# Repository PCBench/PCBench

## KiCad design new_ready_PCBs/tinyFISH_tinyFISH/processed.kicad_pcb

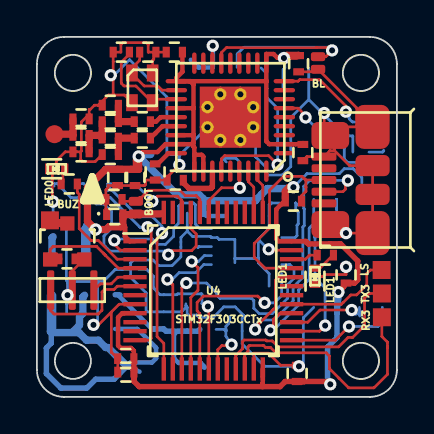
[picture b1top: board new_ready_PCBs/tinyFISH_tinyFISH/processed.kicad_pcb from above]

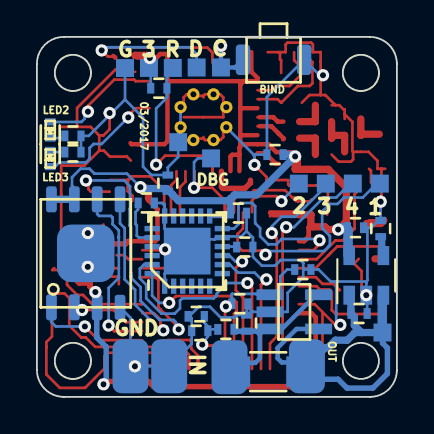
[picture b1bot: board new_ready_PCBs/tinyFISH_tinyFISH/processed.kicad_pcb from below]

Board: 2 copper layers, 20.0 x 20.0 mm, 87 parts (40 on the bottom side), 56 nets.

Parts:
ANT1: TP; smd_1x1_round
BIND1: CUSTOM_PUSHBUTTON; OMRON_B3U-3000P
BL1: BL; SOLDERBRIDGE
C1, C10, C17, C23: 1u; C_0402_CUSTOM
C2, C6: 12p; C_0402_CUSTOM
C3, C13, C14, C16, C19, C20, C21, C22, C25, C26, C27, C29: 100n; C_0402_CUSTOM
C4, C7: 100p; C_0402_CUSTOM
C5: 220p; C_0402_CUSTOM
C8, C9: 1p; C_0402_CUSTOM
C11: 1p8; C_0402_CUSTOM
C12: 1p5; C_0402_CUSTOM
C15: 2n2; C_0402_CUSTOM
C18: 4u7; C_0402_CUSTOM
C24, C30: 10n; C_0402_CUSTOM
C28: NC; C_0402_CUSTOM
DEBUG1: TP; TP_1x1
GND_IN1: GND; PAD_2x3
GND_MOUNT_2: GND; TP_1x1
GND_OUT1: GND; PAD_2x3
H1, H2, H3, H4: hole; mouting_hole
ISP_3V1: TP; TP_1x1
ISP_CLOCK1: TP; TP_1x1
ISP_DATA1: TP; TP_1x1
ISP_GND1: TP; TP_1x1
JP0: BOOT0; SOLDERBRIDGE
L1, L2, L3: 1.2nH; L_0402_CUSTOM
LED0: BLUE; LED_0402
LED1, LED3: RED; LED_0402
LED2: GREEN; LED_0402
Q1: SI2302DS; SI2302DS_SOT-23
R1, R5, R10: 10k; R_0402_CUSTOM
R3: 56k; R_0402_CUSTOM
R4: 220; R_0402_CUSTOM
R6, R8: 330; R_0402_CUSTOM
R7: 100; R_0402_CUSTOM
R9: 1k5; R_0402_CUSTOM
R11, R501: 1k; R_0402_CUSTOM
R12: 0R005; R_1206
R13: 30k; R_0402_CUSTOM
TP_1: WS2812; TP_1x1
TP_2: UART3_RX; TP_1x1
TP_3: UART3_RX1; TP_1x1
TP_4: BUZZER_GND; TP_1x1
TP_5: BUZZER_VCC; TP_1x1
TP_ESC_0: ESC_0; TP_1x1
TP_ESC_1: ESC_1; TP_1x1
TP_ESC_2: ESC_2; TP_1x1
TP_ESC_3: ESC_3; TP_1x1
U1: CC2510; QFN36_CC2510
U2: MPU-6000; QFN-24
U3: LP2985AIM5-3.0/NOPB; SOT-23-5
U4: STM32F303CCTx; LQFP-48_7x7mm_Pitch0.5mm
U5: M25P16-VME; VFDFPN8
U6: MICRO_USB_B; USB_MICRO_MOLEX
U7: INA139; DBV
VBAT1: CONN_1; PAD_2x3
VBAT_IN1: CONN_1; PAD_2x3
X1: 26MHz; crystal_2016
X2: 8MHz; CSTCE_G_A

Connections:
3V: C3.1, C5.1, C10.1, C13.1, C16.2, C18.1, C19.1, C20.1, C21.1, C22.1, C23.1, C24.1, C25.1, C29.1, ISP_3V1.1, JP0.1, R5.1, R9.1, U1.2, U1.10, U1.19, U1.22, U1.25, U1.26, U1.28, U1.29, U2.13, U3.5, U4.1, U4.9, U4.24, U4.36, U4.48, U5.3, U5.7, U5.8
/power/BAT+: C26.2, R10.2, R12.1, U7.3, U7.5, VBAT_IN1.1
/rx/ANT_N: C4.1, U1.24
/rx/ANT_P: C7.1, U1.23
/rx/ISP_CLOCK: BIND1.1, ISP_CLOCK1.1, U1.16
/rx/ISP_DATA: BL1.1, ISP_DATA1.1, U1.15
/rx/~RESET: R5.2, U1.31
ADC_CURRENT: C28.2, R13.1, U4.18, U7.1
ADC_VBAT: C27.1, R10.1, R11.2, U4.19
BUZZER: Q1.D, TP_4.1
BUZZER_IO: Q1.G, R501.2, U4.4
ESC_0: TP_ESC_0.1, U4.45
ESC_1: TP_ESC_1.1, U4.46
ESC_2: TP_ESC_2.1, U4.13
ESC_3: TP_ESC_3.1, U4.12
FLASH_CS: U4.25, U5.1
FLASH_MISO: U4.27, U5.2
FLASH_MOSI: U4.28, U5.5
FLASH_SCK: U4.26, U5.6
GND: BIND1.2, BL1.2, C1.1, C2.2, C3.2, C5.2, C6.2, C8.1, C10.2, C11.1, C12.1, C13.2, C14.2, C15.1, C16.1, C17.2, C18.2, C19.2, C20.2, C21.2, C22.2, C23.2, C24.2, C25.2, C26.1, C27.2, C28.1, C29.2, C30.2, GND_IN1.1, GND_MOUNT_2.1, GND_OUT1.1, ISP_GND1.1, L1.1, LED0.1, LED1.1, Q1.S, R1.2, R3.1, R4.2, R6.2, R11.1, R13.2, R501.1, U1.GND, U2.1, U2.11, U2.18, U3.2, U4.8, U4.23, U4.35, U5.4, U6.5, U7.2, X1.2, X1.4, X2.2
LED_0: R7.1, U4.3
LED_1: R8.1, U4.34
MPU_EXTI: U2.12, U4.2
MPU_SPI_CS: U2.8, U4.14
MPU_SPI_MISO: U2.9, U4.16
MPU_SPI_MOSI: U2.24, U4.17
MPU_SPI_SCK: U2.23, U4.15
unnamed: ANT1.1, C12.2, L3.2
unnamed: C1.2, U1.30
unnamed: C2.1, U1.20, X1.1
unnamed: C4.2, C9.1, L1.2
unnamed: C6.1, U1.21, X1.3
unnamed: C7.2, C8.2, L2.1
unnamed: C9.2, C11.2, L2.2, L3.1
unnamed: C14.1, U2.10
unnamed: C15.2, U2.20
unnamed: C30.1, U3.4
unnamed: JP0.2, R1.1, U4.44
unnamed: LED0.2, R7.2
unnamed: LED1.2, R8.2
unnamed: LED2.1, R4.1
unnamed: LED2.2, U1.9
unnamed: LED3.1, R6.1
unnamed: LED3.2, U1.6
unnamed: R3.2, U1.27
unnamed: R9.2, U4.33, U6.3
unnamed: U4.5, X2.1
unnamed: U4.6, X2.3
unnamed: U4.32, U6.2
RX_DEBUG: DEBUG1.1, U1.33, U4.43
RX_HUB_TELEMETRY: U1.35, U4.37
RX_SBUS: U1.34, U4.38
UART3_RX: TP_3.1, U4.22
UART3_TX: TP_2.1, U4.21
VBAT: C17.1, R12.2, TP_5.1, U3.1, U3.3, U7.4, VBAT1.1
WS2812: TP_1.1, U4.29

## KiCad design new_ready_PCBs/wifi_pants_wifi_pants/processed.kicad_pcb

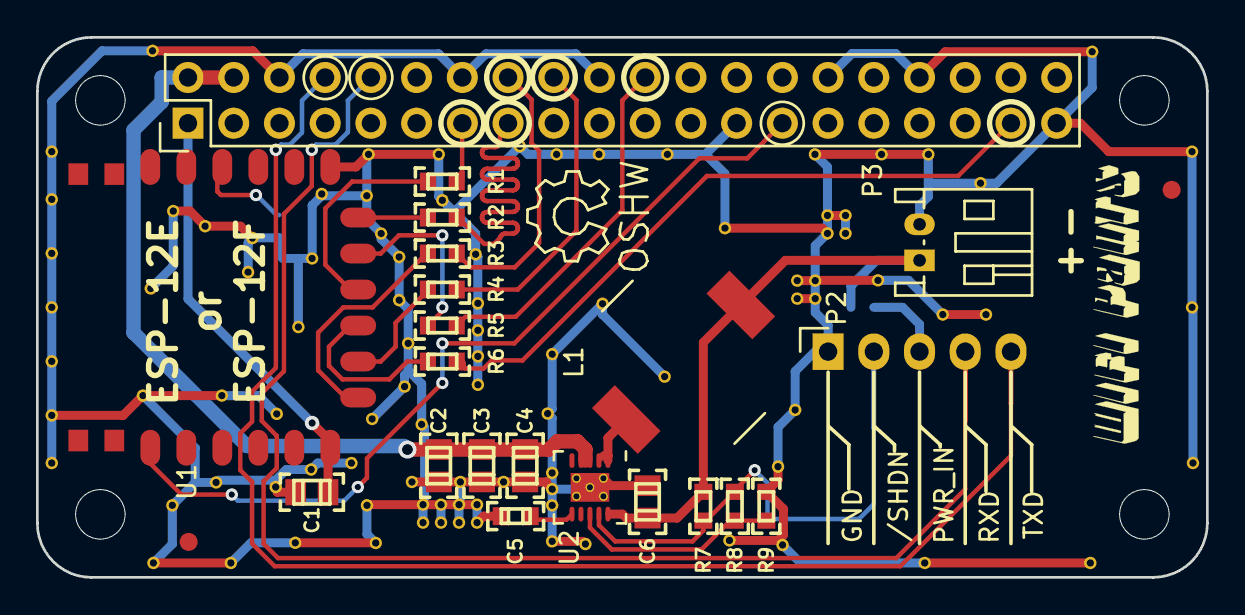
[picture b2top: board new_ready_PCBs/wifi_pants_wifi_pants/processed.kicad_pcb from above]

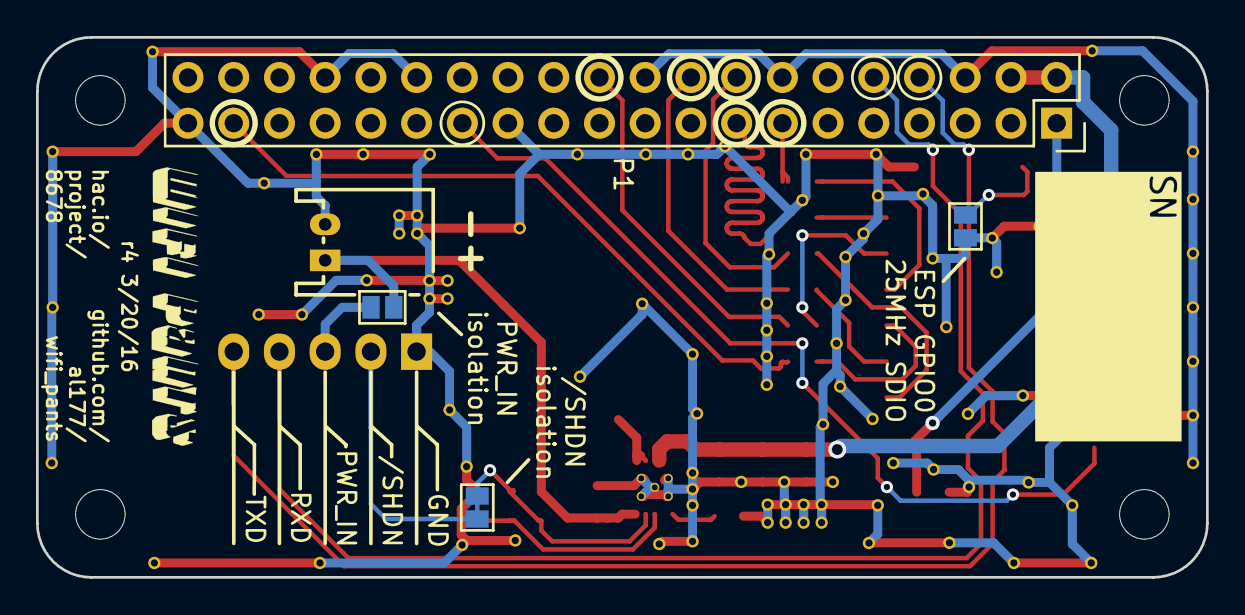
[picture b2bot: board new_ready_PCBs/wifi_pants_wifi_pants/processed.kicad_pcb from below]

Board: 2 copper layers, 65.0 x 30.0 mm, 28 parts (4 on the bottom side), 25 nets.

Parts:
C1, C2, C3, C4: 10uF X5R; 0805(2012m)-CHIP-CAP
C5: 0.15uF X5R; 0603(1608m)-CHIP-CAP
C6: 22uF X5R; 0805(2012m)-CHIP-CAP
JP1: /PSU_SHDN ISOL; GS2
JP2: PWR_IN ISOL; GS2
JP3: GPIO0; GS2
L1: 1.0uH; SRU1028-1R
P1: CONN_02X20; Socket_Strip_Straight_2x20_pi
P2: POWER / UART; Pin_Header_Angled_1x05_mirror
P3: JST PH POWER IN; Connectors_JST_S2B-PH-K
R1, R2, R3, R4, R5, R6: 33; 0603(1608m)-CHIP-RESISTOR
R7: 47K 1%; 0603(1608m)-CHIP-RESISTOR
R8: 33K 1%; 0603(1608m)-CHIP-RESISTOR
R9: 1K 1%; 0603(1608m)-CHIP-RESISTOR
U1: ESP-12E; ESP-12E-narrow
U2: TPS6123x; VSON-10
W1, W1_2, W1_3, W1_4: MOUNT; NPTH_Hole_2_75mm

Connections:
+3V3: C1.1, P1.1, U1.8
+5V: C2.1, C3.1, C4.1, P1.2, P1.4, U2.3, U2.4
//CS: R3.2, U1.9
//HOLD: R6.2, U1.11
//WP: R1.2, U1.12
/CLK: R2.2, U1.14
/SHDN: JP1.1, JP1.2, P2.2, R7.2, R8.1, U2.9
/SI: R5.2, U1.13
/SO: R4.2, U1.10
GND: C1.2, C2.2, C3.2, C4.2, C5.2, C6.2, JP3.2, P1.6, P1.14, P1.20, P1.25, P1.30, P1.34, P1.39, P2.1, P3.2, R9.2, U1.15, U2.11
ID_SD: P1.27, U1.3
unnamed: C5.1, U2.6
unnamed: JP2.2, P2.3
unnamed: JP3.1, U1.18
unnamed: L1.2, U2.1, U2.2
unnamed: R8.2, R9.1, U2.8
PI_UART0_RXD: P1.10, P2.4
PI_UART0_TXD: P1.8, P2.5
PWR_IN: C6.1, JP2.1, L1.1, P3.1, R7.1, U2.10
SD_CLK: P1.15, R2.1
SD_CMD: P1.16, R3.1
SD_D0: P1.18, R4.1
SD_D1: P1.22, R5.1
SD_D2: P1.37, R6.1
SD_D3: P1.13, R1.1

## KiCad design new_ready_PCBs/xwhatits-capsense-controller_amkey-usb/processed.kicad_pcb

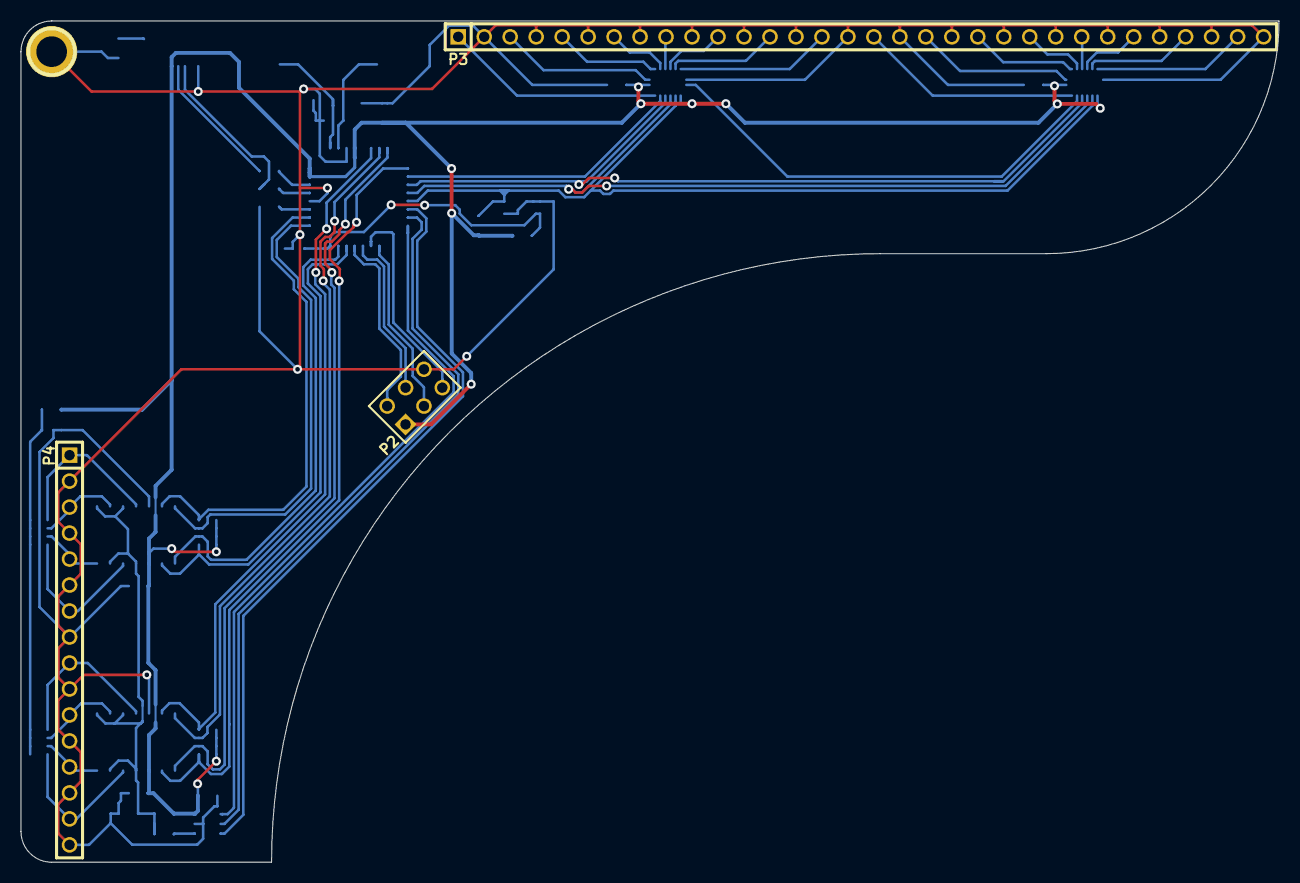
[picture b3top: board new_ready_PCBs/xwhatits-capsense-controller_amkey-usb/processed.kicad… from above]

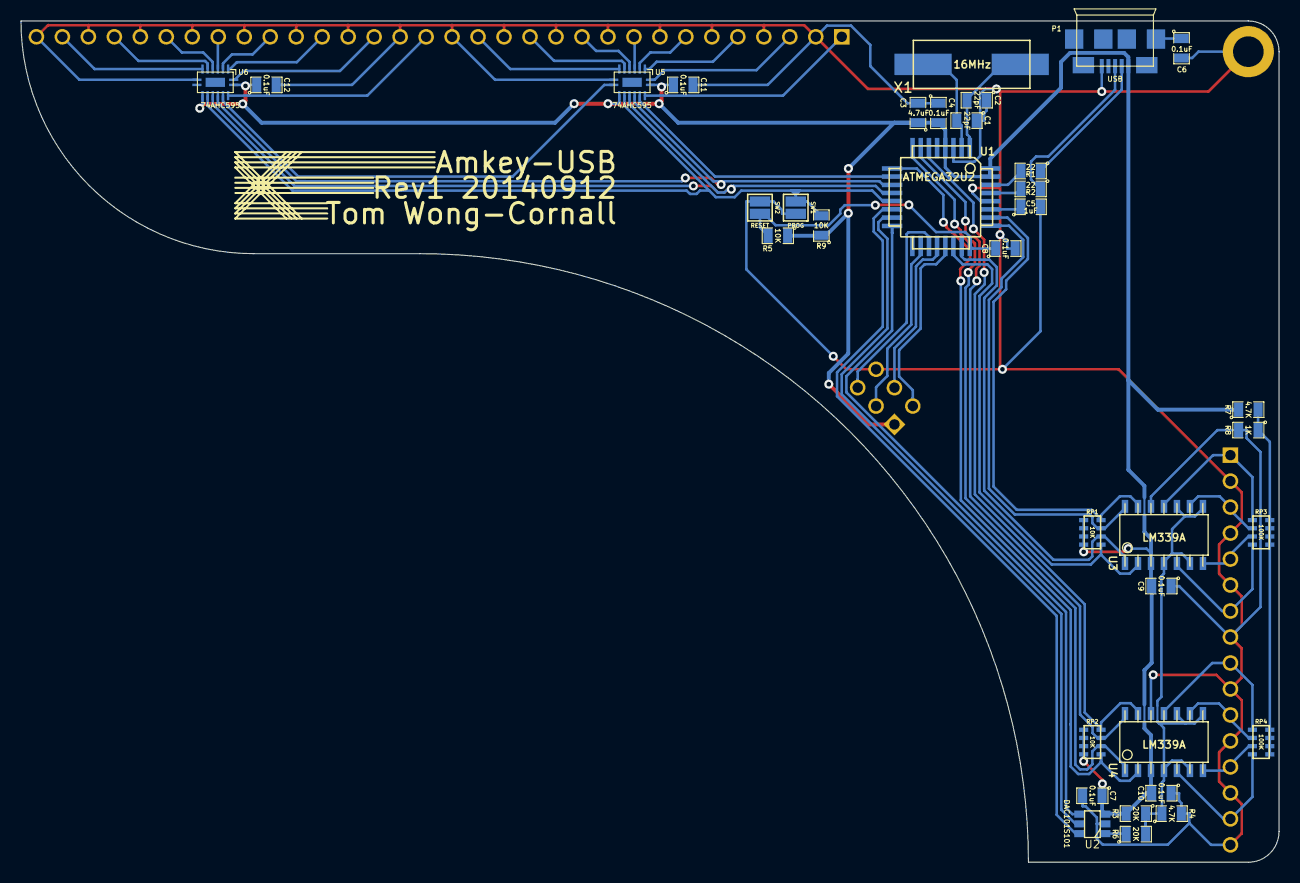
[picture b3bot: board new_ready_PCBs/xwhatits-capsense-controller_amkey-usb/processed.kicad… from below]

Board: 2 copper layers, 123.0 x 82.2 mm, 39 parts (35 on the bottom side), 58 nets.

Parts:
1PIN: P***; 1pin
C1, C2: 22pF; SM0805
C3: 4.7uF; SM0805
C4, C6, C7, C8, C9, C10, C11, C12: 0.1uF; SM0805
C5: 1uF; SM0805
P1: USB; USB-Micro-B-SMT
P2: CONN_3X2; pin_array_3x2
P3: Columns; PIN_ARRAY-32X1
P4: Rows; PIN_ARRAY-16X1
R1, R2: 22; SM0805
R3, R6: 20K; SM0805
R4, R7: 4.7K; SM0805
R5, R9: 10K; SM0805
R8: 1K; SM0805
RP1, RP2: 10K; RPACK_1206
RP3, RP4: 100K; RPACK_1206
SW1: PROG; TEST_BRIDGE_SM
SW2: RESET; TEST_BRIDGE_SM
U1: ATMEGA32U2; TQFP32
U2: DAC101S101; SOT23_6
U3, U4: LM339A; so-14
U5, U6: 74AHC595; DHVQFN16
X1: 16MHz; HC49US

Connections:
/SPI_MOSI: U1.16, U2.4
/SPI_SCLK: U1.15, U2.5
/SPI_SS: U1.14, U2.6
/USB_D+: P1.3, R2.1
/USB_D-: P1.2, R1.1
/USB_SHIELD: C6.1, P1.6
Col1: P3.1, U5.15
Col2: P3.3, U5.1
Col3: P3.5, U5.2
Col4: P3.7, U5.3
Col5: P3.9, U5.4
Col6: P3.11, U5.5
Col7: P3.13, U5.6
Col8: P3.15, U5.7
Col9: P3.17, U6.15
Col10: P3.19, U6.1
Col11: P3.21, U6.2
Col12: P3.23, U6.3
Col13: P3.25, U6.4
Col14: P3.27, U6.5
Col15: P3.29, U6.6
Col16: P3.31, U6.7
GND: 1PIN.1, C1.1, C2.1, C3.2, C4.1, C5.2, C6.2, C7.2, C8.2, C9.1, C10.1, C11.2, C12.2, P1.5, P2.6, P3.2, P3.4, P3.6, P3.8, P3.10, P3.12, P3.14, P3.16, P3.18, P3.20, P3.22, P3.24, P3.26, P3.28, P3.30, P3.32, P4.2, P4.4, P4.6, P4.8, P4.10, P4.12, P4.14, P4.16, R4.2, R8.2, SW1.1, SW2.2, U1.3, U1.28, U2.2, U3.12, U4.12, U5.8, U6.8
unnamed: R2.2, U1.29
unnamed: R1.2, U1.30
unnamed: C5.1, U1.27
unnamed: C2.2, U1.1, X1.2
unnamed: R3.1, R4.1, R6.2, U3.4, U3.6, U3.8, U3.10, U4.4, U4.6, U4.8, U4.10
unnamed: C8.1, R5.2, SW2.1, U1.24
unnamed: P2.4, U1.20
unnamed: P2.5, U1.19
unnamed: P2.3, U1.18
unnamed: P2.2, U1.21
unnamed: U5.9, U6.14
unnamed: R6.1, U2.1
unnamed: R7.2, R8.1, RP3.1, RP3.2, RP3.3, RP3.4, RP4.1, RP4.2, RP4.3, RP4.4
unnamed: C1.2, U1.2, X1.1
Row1: P4.1, RP3.5, U3.11
Row2: P4.3, RP3.6, U3.9
Row3: P4.5, RP3.7, U3.7
Row4: P4.7, RP3.8, U3.5
Row5: P4.9, RP4.5, U4.11
Row6: P4.11, RP4.6, U4.9
Row7: P4.13, RP4.7, U4.7
Row8: P4.15, RP4.8, U4.5
RowOP1: RP1.4, U1.26, U3.13
RowOP2: RP1.3, U1.25, U3.14
RowOP3: RP1.2, U1.23, U3.1
RowOP4: RP1.1, U1.22, U3.2
RowOP5: RP2.4, U1.6, U4.13
RowOP6: RP2.3, U1.7, U4.14
RowOP7: RP2.2, U1.8, U4.1
RowOP8: RP2.1, U1.9, U4.2
SR_DS: U1.10, U5.14
SR_OE: U1.11, U5.13, U6.13
SR_SHCP: R9.2, SW1.2, U1.13, U5.11, U6.11
SR_STCP: U1.12, U5.12, U6.12
VCC: C3.1, C4.2, C7.1, C9.2, C10.2, C11.1, C12.1, P1.1, P2.1, R3.2, R5.1, R7.1, R9.1, RP1.5, RP1.6, RP1.7, RP1.8, RP2.5, RP2.6, RP2.7, RP2.8, U1.4, U1.31, U1.32, U2.3, U3.3, U4.3, U5.10, U5.16, U6.10, U6.16

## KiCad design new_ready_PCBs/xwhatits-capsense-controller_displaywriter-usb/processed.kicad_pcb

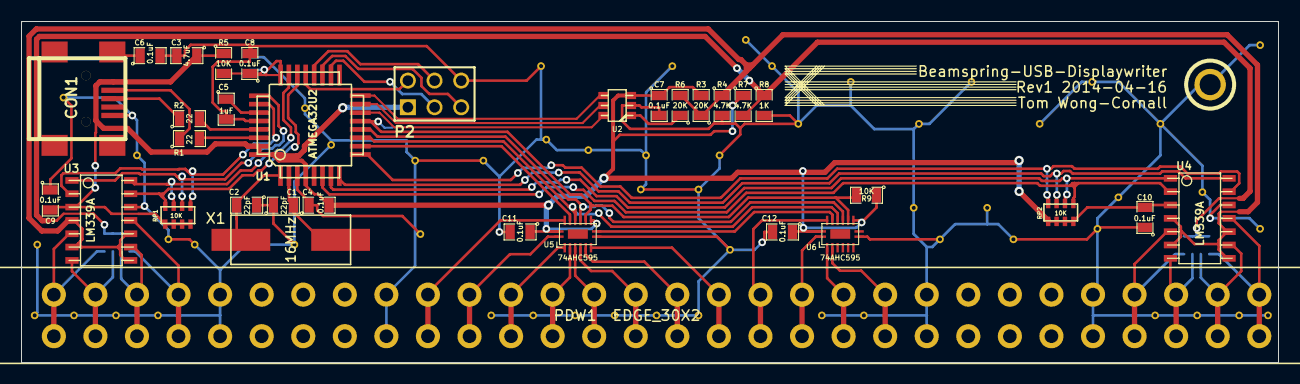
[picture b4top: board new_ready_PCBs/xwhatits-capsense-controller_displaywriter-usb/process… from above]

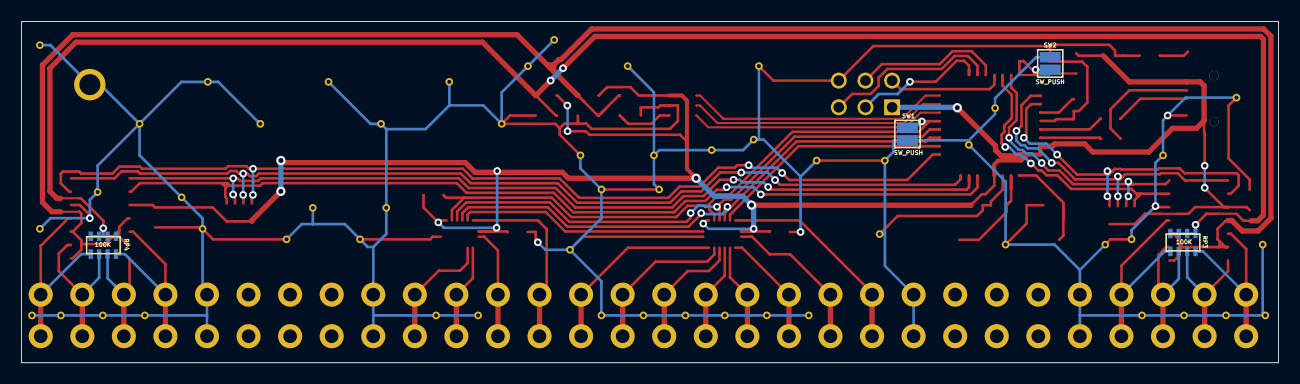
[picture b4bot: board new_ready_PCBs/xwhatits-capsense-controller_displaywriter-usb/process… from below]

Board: 2 copper layers, 119.8 x 32.5 mm, 92 parts (4 on the bottom side), 54 nets.

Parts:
., ._2, ._3, ._4, ._5, ._6, ._7, ._8, ._9, ._10, ._11, ._12, ._13, ._14, ._15, ._16, ._17, ._18, ._19, ._20, ._21, ._22, ._23, ._24, ._25, ._26, ._27, ._28, ._29, ._30, ._31, ._32, ._33, ._34, ._35, ._36, ._37, ._38, ._39, ._40, ._41, ._42, ._43, ._44, ._45, ._46, ._47, ._48, ._49, ._50, ._51, ._52, ._53, ._54: .; Via
C1, C2: 22pF; SM0805
C3: 4.7uF; SM0805
C4, C6, C7, C8, C9, C10, C11, C12: 0.1uF; SM0805
C5: 1uF; SM0805
CON1: USB-MINI-B; USB_MINI_B
P2: CONN_3X2; pin_array_3x2
P3: Chassis GND; 1pin
PDW1: EDGE_30X2; 805_396_30x2_pins
R1, R2: 22; SM0805
R3, R6: 20K; SM0805
R4, R7: 4.7K; SM0805
R5, R9: 10K; SM0805
R8: 1K; SM0805
RP1, RP2: 10K; RPACK_1206
RP3, RP4: 100K; RPACK_1206
SW1, SW2: SW_PUSH; TEST_BRIDGE_SM
U1: ATMEGA32U2; TQFP32
U2: DAC101S101; tsot-6
U3, U4: LM339A; so-14
U5, U6: 74AHC595; DHVQFN16
X1: 16MHz; HC49US

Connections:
/SPI_MOSI: U1.16, U2.4
/SPI_SCLK: U1.15, U2.5
/SPI_SS: U1.14, U2.6
Col1: PDW1.10, PDW1.40, U5.15
Col2: PDW1.11, PDW1.41, U5.1
Col3: PDW1.12, PDW1.42, U5.2
Col4: PDW1.13, PDW1.43, U5.3
Col5: PDW1.14, PDW1.44, U5.4
Col6: PDW1.15, PDW1.45, U5.5
Col7: PDW1.16, PDW1.46, U5.6
Col8: PDW1.17, PDW1.47, U5.7
Col9: PDW1.18, PDW1.48, U6.15
Col10: PDW1.19, PDW1.49, U6.1
Col11: PDW1.20, PDW1.50, U6.2
Col12: PDW1.21, PDW1.51, U6.3
GND: C1.1, C2.1, C3.2, C4.1, C5.2, C6.2, C7.2, C8.2, C9.1, C10.1, C11.2, C12.2, CON1.5, P2.6, P3.1, PDW1.5, PDW1.9, PDW1.22, PDW1.26, PDW1.35, PDW1.39, PDW1.52, PDW1.56, R4.2, R8.2, SW1.1, SW2.2, U1.3, U1.28, U2.2, U3.12, U4.12, U5.8, U6.8
unnamed: U5.9, U6.14
unnamed: C6.1, CON1.6
unnamed: R6.1, U2.1
unnamed: C2.2, U1.1, X1.2
unnamed: C5.1, U1.27
unnamed: C8.1, R5.2, SW2.1, U1.24
unnamed: R3.1, R4.1, R6.2, U3.4, U3.6, U3.8, U3.10, U4.4, U4.6, U4.8, U4.10
unnamed: CON1.3, R2.1
unnamed: CON1.2, R1.1
unnamed: R2.2, U1.29
unnamed: R1.2, U1.30
unnamed: P2.5, U1.19
unnamed: P2.3, U1.18
unnamed: P2.2, U1.21
unnamed: P2.4, U1.20
unnamed: R7.2, R8.1, RP3.1, RP3.2, RP3.3, RP3.4, RP4.1, RP4.2, RP4.3, RP4.4
unnamed: C1.2, U1.2, X1.1
Row1: PDW1.1, PDW1.31, RP3.8, U3.5
Row2: PDW1.2, PDW1.32, RP3.7, U3.7
Row3: PDW1.3, PDW1.33, RP3.6, U3.9
Row4: PDW1.4, PDW1.34, RP3.5, U3.11
Row5: PDW1.27, PDW1.57, RP4.8, U4.5
Row6: PDW1.28, PDW1.58, RP4.7, U4.7
Row7: PDW1.29, PDW1.59, RP4.6, U4.9
Row8: PDW1.30, PDW1.60, RP4.5, U4.11
RowOP1: RP1.1, U1.26, U3.2
RowOP2: RP1.2, U1.25, U3.1
RowOP3: RP1.3, U1.23, U3.14
RowOP4: RP1.4, U1.22, U3.13
RowOP5: RP2.1, U1.6, U4.2
RowOP6: RP2.2, U1.7, U4.1
RowOP7: RP2.3, U1.8, U4.14
RowOP8: RP2.4, U1.9, U4.13
SR_DS: U1.10, U5.14
SR_OE: U1.11, U5.13, U6.13
SR_SHCP: R9.2, SW1.2, U1.13, U5.11, U6.11
SR_STCP: U1.12, U5.12, U6.12
VCC: C3.1, C4.2, C7.1, C9.2, C10.2, C11.1, C12.1, CON1.1, P2.1, R3.2, R5.1, R7.1, R9.1, RP1.5, RP1.6, RP1.7, RP1.8, RP2.5, RP2.6, RP2.7, RP2.8, U1.4, U1.31, U1.32, U2.3, U3.3, U4.3, U5.10, U5.16, U6.10, U6.16

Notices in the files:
new_ready_PCBs/wifi_pants_wifi_pants/processed.kicad_pcb:
Licensed under Creative Commons Attribution Share-Alike
